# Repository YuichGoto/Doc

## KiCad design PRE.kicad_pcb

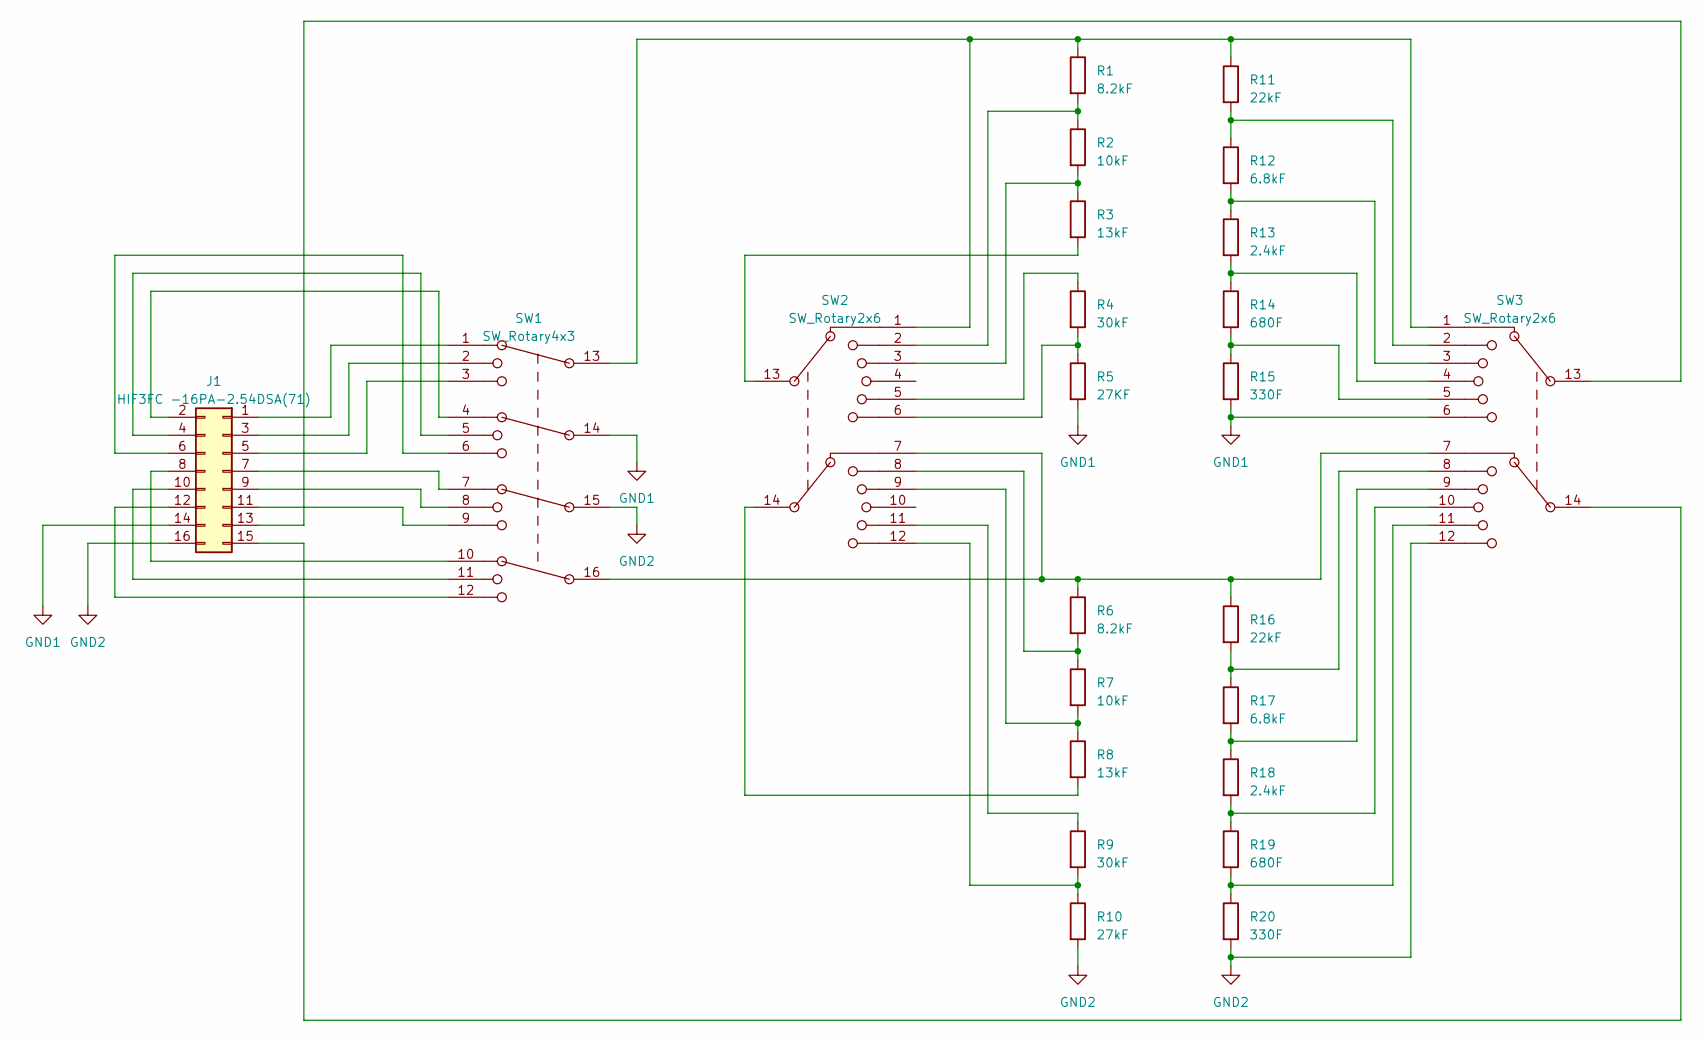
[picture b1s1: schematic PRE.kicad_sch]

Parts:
J1: HIF3FC -16PA-2.54DSA(71); PinHeader_2x08_P2.54mm_Vertical
R1, R6: 8.2kF; R_Axial_DIN0207_L6.3mm_D2.5mm_P10.16mm_Horizontal
R2, R7: 10kF; R_Axial_DIN0207_L6.3mm_D2.5mm_P10.16mm_Horizontal
R3, R8: 13kF; R_Axial_DIN0207_L6.3mm_D2.5mm_P10.16mm_Horizontal
R4, R9: 30kF; R_Axial_DIN0207_L6.3mm_D2.5mm_P10.16mm_Horizontal
R5: 27KF; R_Axial_DIN0207_L6.3mm_D2.5mm_P10.16mm_Horizontal
R10: 27kF; R_Axial_DIN0207_L6.3mm_D2.5mm_P10.16mm_Horizontal
R11, R16: 22kF; R_Axial_DIN0207_L6.3mm_D2.5mm_P10.16mm_Horizontal
R12, R17: 6.8kF; R_Axial_DIN0207_L6.3mm_D2.5mm_P10.16mm_Horizontal
R13, R18: 2.4kF; R_Axial_DIN0207_L6.3mm_D2.5mm_P10.16mm_Horizontal
R14, R19: 680F; R_Axial_DIN0207_L6.3mm_D2.5mm_P10.16mm_Horizontal
R15, R20: 330F; R_Axial_DIN0207_L6.3mm_D2.5mm_P10.16mm_Horizontal
SW1: SW_Rotary4x3
SW2, SW3: SW_Rotary2x6

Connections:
GND1: J1.14, R5.2, R15.2, SW1.14, SW3.6
GND2: J1.16, R10.2, R20.2, SW1.15, SW3.12
unnamed: J1.1, SW1.1
unnamed: J1.2, SW1.4
unnamed: J1.3, SW1.2
unnamed: J1.4, SW1.5
unnamed: J1.5, SW1.3
unnamed: J1.6, SW1.6
unnamed: J1.7, SW1.7
unnamed: J1.8, SW1.10
unnamed: J1.9, SW1.8
unnamed: J1.10, SW1.11
unnamed: J1.11, SW1.9
unnamed: J1.12, SW1.12
unnamed: J1.13, SW3.13
unnamed: J1.15, SW3.14
unnamed: R1.1, R11.1, SW1.13, SW2.1, SW3.1
unnamed: R1.2, R2.1, SW2.2
unnamed: R2.2, R3.1, SW2.3
unnamed: R3.2, SW2.13
unnamed: R4.1, SW2.5
unnamed: R4.2, R5.1, SW2.6
unnamed: R6.2, R7.1, SW2.8
unnamed: R7.2, R8.1, SW2.9
unnamed: R8.2, SW2.14
unnamed: R9.1, SW2.11
unnamed: R9.2, R10.1, SW2.12
unnamed: R11.2, R12.1, SW3.2
unnamed: R12.2, R13.1, SW3.3
unnamed: R13.2, R14.1, SW3.4
unnamed: R14.2, R15.1, SW3.5
unnamed: R6.1, R16.1, SW1.16, SW2.7, SW3.7
unnamed: R16.2, R17.1, SW3.8
unnamed: R17.2, R18.1, SW3.9
unnamed: R18.2, R19.1, SW3.10
unnamed: R19.2, R20.1, SW3.11

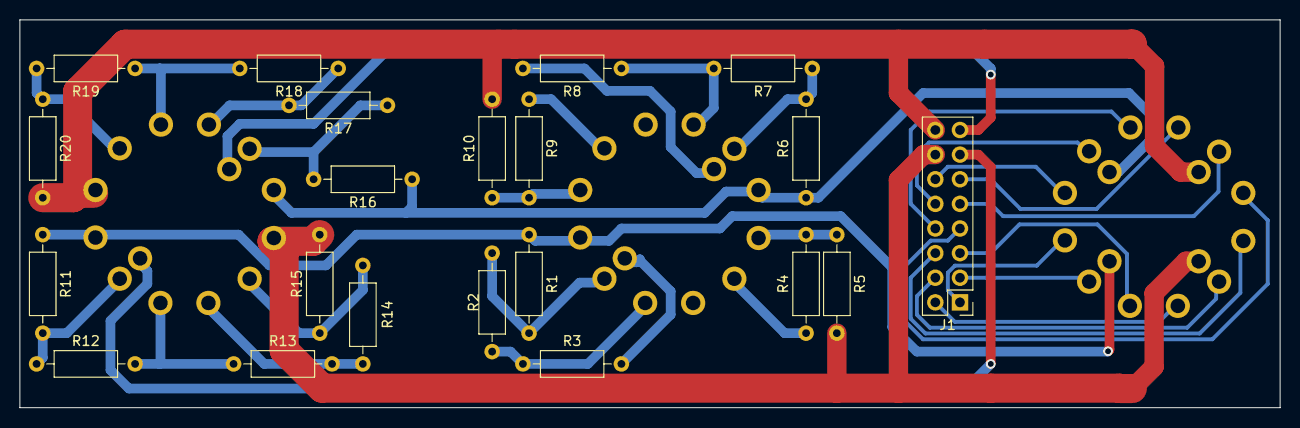
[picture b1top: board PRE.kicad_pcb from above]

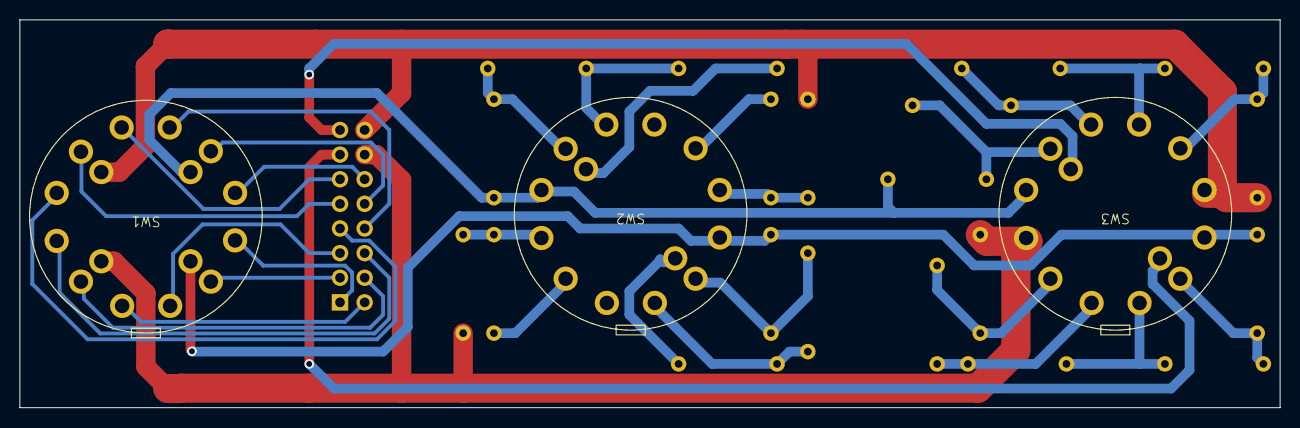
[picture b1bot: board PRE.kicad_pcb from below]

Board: 2 copper layers, 130.0 x 40.0 mm, 24 parts (3 on the bottom side), 36 nets.

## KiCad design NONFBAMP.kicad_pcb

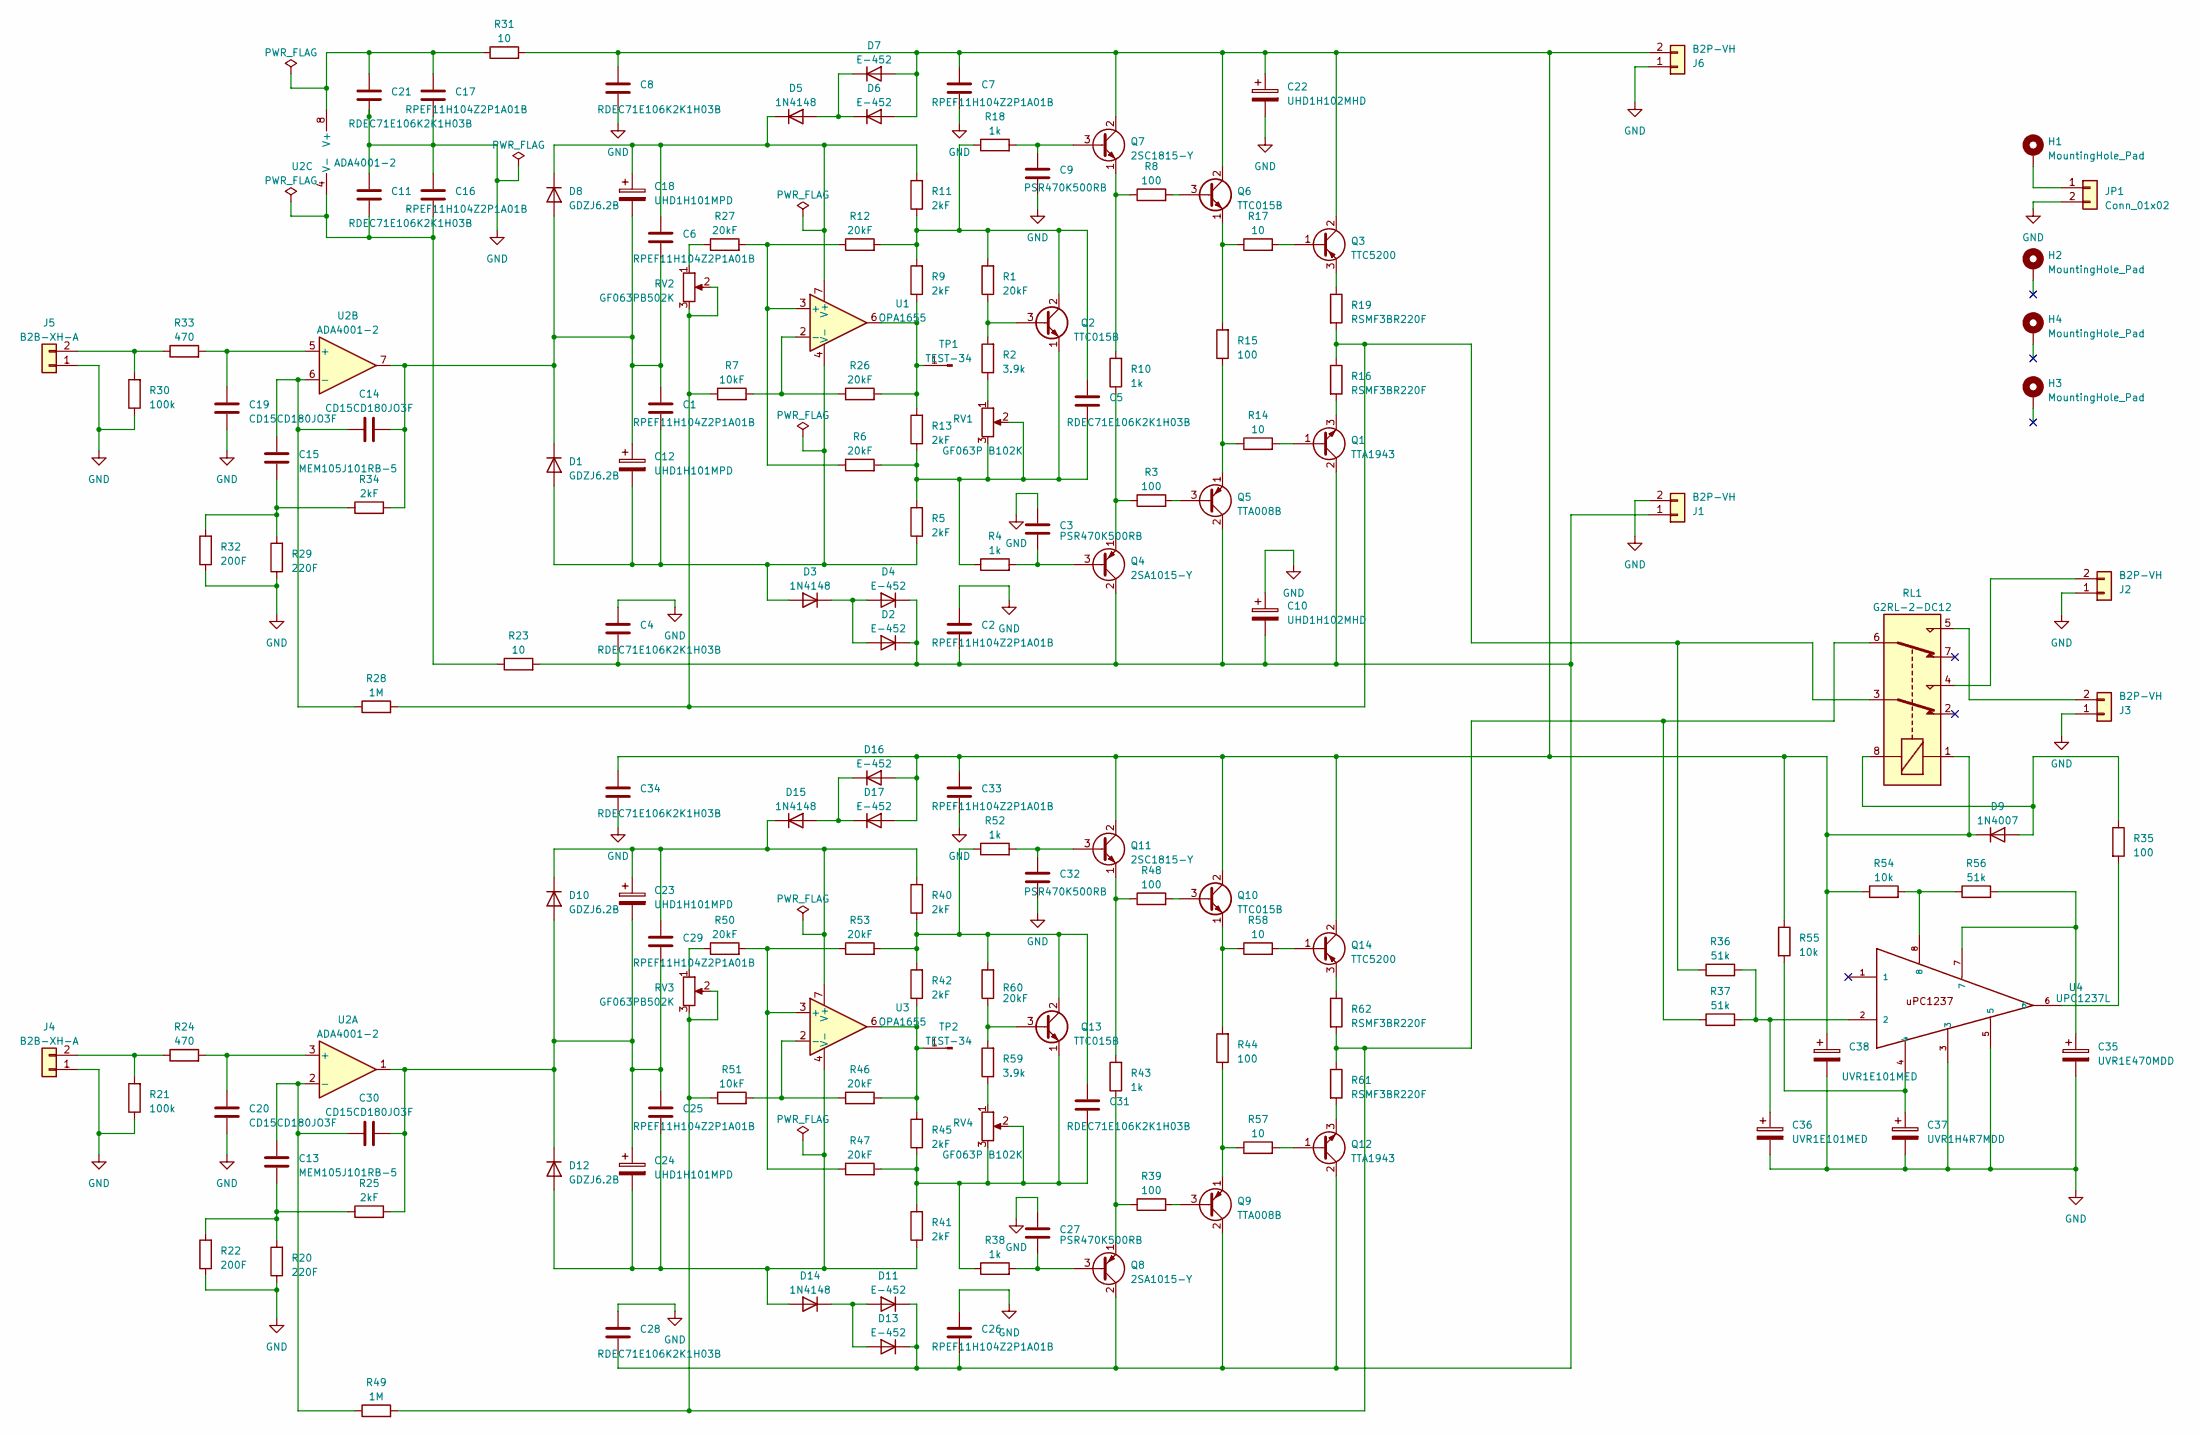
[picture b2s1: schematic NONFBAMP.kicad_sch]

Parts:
C1, C2, C6, C7, C16, C17, C25, C26, C29, C33: RPEF11H104Z2P1A01B; C_Disc_D5.0mm_W2.5mm_P2.50mm
C3, C9, C27, C32: PSR470K500RB; C_Disc_D5.0mm_W2.5mm_P5.00mm
C4, C5, C8, C11, C21, C28, C31, C34: RDEC71E106K2K1H03B; C_Disc_D5.0mm_W2.5mm_P5.00mm
C10, C22: UHD1H102MHD; CP_Radial_D16.0mm_P7.50mm
C12, C18, C23, C24: UHD1H101MPD; CP_Radial_D8.0mm_P3.50mm
C13, C15: MEM105J101RB-5; C_Rect_L7.2mm_W5.5mm_P5.00mm_FKS2_FKP2_MKS2_MKP2
C14, C19, C20, C30: CD15CD180JO3F; C_Disc_D10.5mm_W5.0mm_P5.00mm
C35: UVR1E470MDD; CP_Radial_D5.0mm_P2.50mm
C36, C38: UVR1E101MED; CP_Radial_D6.3mm_P2.50mm
C37: UVR1H4R7MDD; CP_Radial_D5.0mm_P2.50mm
D1, D8, D10, D12: GDZJ6.2B; D_DO-35_SOD27_P7.62mm_Horizontal
D2, D4, D6, D7, D11, D13, D16, D17: E-452; D_DO-35_SOD27_P7.62mm_Horizontal
D3, D5, D14, D15: 1N4148; D_DO-35_SOD27_P7.62mm_Horizontal
D9: 1N4007; D_DO-41_SOD81_P10.16mm_Horizontal
H1, H2, H3, H4: MountingHole_Pad; MountingHole_3.2mm_M3_DIN965_Pad
J1, J2, J3, J6: B2P-VH; JST_VH_B2P-VH_1x02_P3.96mm_Vertical
J4, J5: B2B-XH-A; JST_XH_B2B-XH-A_1x02_P2.50mm_Vertical
JP1: Conn_01x02; PinHeader_1x02_P2.54mm_Vertical
Q1, Q12: TTA1943; TO-3PB-3_Vertical
Q2, Q6, Q10, Q13: TTC015B; TO-126-3_Vertical
Q3, Q14: TTC5200; TO-3PB-3_Vertical
Q4, Q8: 2SA1015-Y; TO-92
Q5, Q9: TTA008B; TO-126-3_Vertical
Q7, Q11: 2SC1815-Y; TO-92
R1, R6, R12, R26, R27, R46, R47, R50, R53, R60: 20kF; R_Axial_DIN0204_L3.6mm_D1.6mm_P5.08mm_Horizontal
R2, R59: 3.9k; R_Axial_DIN0204_L3.6mm_D1.6mm_P5.08mm_Horizontal
R3, R8, R15, R35, R39, R44, R48: 100; R_Axial_DIN0204_L3.6mm_D1.6mm_P5.08mm_Horizontal
R4, R10, R18, R38, R43, R52: 1k; R_Axial_DIN0204_L3.6mm_D1.6mm_P5.08mm_Horizontal
R5, R9, R11, R13, R25, R34, R40, R41, R42, R45: 2kF; R_Axial_DIN0204_L3.6mm_D1.6mm_P5.08mm_Horizontal
R7, R51: 10kF; R_Axial_DIN0204_L3.6mm_D1.6mm_P5.08mm_Horizontal
R14, R17, R23, R31, R57, R58: 10; R_Axial_DIN0204_L3.6mm_D1.6mm_P5.08mm_Horizontal
R16, R19, R61, R62: RSMF3BR220F; R_Axial_DIN0516_L15.5mm_D5.0mm_P20.32mm_Horizontal
R20, R29: 220F; R_Axial_DIN0204_L3.6mm_D1.6mm_P5.08mm_Horizontal
R21, R30: 100k; R_Axial_DIN0204_L3.6mm_D1.6mm_P5.08mm_Horizontal
R22, R32: 200F; R_Axial_DIN0204_L3.6mm_D1.6mm_P5.08mm_Horizontal
R24, R33: 470; R_Axial_DIN0204_L3.6mm_D1.6mm_P5.08mm_Horizontal
R28, R49: 1M; R_Axial_DIN0204_L3.6mm_D1.6mm_P5.08mm_Horizontal
R36, R37, R56: 51k; R_Axial_DIN0204_L3.6mm_D1.6mm_P5.08mm_Horizontal
R54, R55: 10k; R_Axial_DIN0204_L3.6mm_D1.6mm_P5.08mm_Horizontal
RL1: G2RL-2-DC12; Relay_DPDT_Omron_G2RL
RV1, RV4: GF063P B102K; Potentiometer_Vishay_T73YP_Vertical
RV2, RV3: GF063PB502K; Potentiometer_Vishay_T73YP_Vertical
TP1, TP2: TEST-34; PinHeader_1x01_P2.00mm_Vertical
U1, U3: OPA1655; SOIC-8_3.9x4.9mm_P1.27mm
U2: ADA4001-2; SOIC-8_3.9x4.9mm_P1.27mm
U4: UPC1237L; SIP-8_19x3mm_P2.54mm

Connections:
GND: C2.1, C3.1, C4.1, C7.2, C8.2, C9.2, C10.1, C11.1, C16.1, C17.2, C19.2, C20.2, C21.2, C22.2, C26.1, C27.1, C28.1, C32.2, C33.2, C34.2, C35.2, C36.2, C37.2, C38.2, J1.2, J2.1, J3.1, J4.1, J5.1, J6.1, JP1.2, R20.1, R21.1, R22.1, R29.1, R30.1, R32.1, U4.3, U4.5
unnamed: C17.1, C21.1, R31.1, U2.8 (V+)
unnamed: C11.2, C16.2, R23.1, U2.4 (V-)
unnamed: C6.1, C18.1, D5.1 (K), D8.1 (K), R11.2, U1.7 (V+)
unnamed: C1.2, C12.2, D1.2 (A), D3.2 (A), R5.1, U1.4 (V-)
unnamed: C23.1, C29.1, D10.1 (K), D15.1 (K), R40.2, U3.7 (V+)
unnamed: C24.2, C25.2, D12.2 (A), D14.2 (A), R41.1, U3.4 (V-)
unnamed: C13.2, R20.2, R22.2, R25.1
unnamed: C15.2, R29.2, R32.2, R34.1
unnamed: C35.1, R56.2, U4.7
unnamed: C36.1, R36.2, R37.2, U4.2
unnamed: C37.1, R55.2, U4.4
unnamed: C1.1, C6.2, C12.1, C14.2, C18.2, D1.1 (K), D8.2 (A), R34.2, U2.7
unnamed: D2.2 (A), D3.1 (K), D4.2 (A)
unnamed: D5.2 (A), D6.1 (K), D7.1 (K)
unnamed: D9.2 (A), R35.1, RL1.8
unnamed: C23.2, C24.1, C25.1, C29.2, C30.2, D10.2 (A), D12.1 (K), R25.2, U2.1
unnamed: D11.2 (A), D13.2 (A), D14.1 (K)
unnamed: C2.2, C4.2, C10.2, C26.2, C28.2, D2.1 (K), D4.1 (K), D11.1 (K), D13.1 (K), J1.1, Q1.2 (C), Q4.2 (C), Q5.2 (C), Q8.2 (C), Q9.2 (C), Q12.2 (C), R23.2
unnamed: D15.2 (A), D16.1 (K), D17.1 (K)
unnamed: C7.1, C8.1, C22.1, C33.1, C34.1, C38.1, D6.2 (A), D7.2 (A), D9.1 (K), D16.2 (A), D17.2 (A), J6.2, Q3.2 (C), Q6.2 (C), Q7.2 (C), Q10.2 (C), Q11.2 (C), Q14.2 (C), R31.2, R54.1, R55.1, RL1.1
unnamed: J2.2, RL1.4
unnamed: J3.2, RL1.5
unnamed: J4.2, R21.2, R24.1
unnamed: J5.2, R30.2, R33.1
unnamed: H1.1, JP1.1
unnamed: Q1.1 (B), R14.2
unnamed: Q1.3 (E), R16.2
unnamed: Q2.3 (B), R1.1, R2.2
unnamed: C5.1, Q2.2 (C), R1.2, R9.2, R11.1, R12.2, R18.1
unnamed: C5.2, Q2.1 (E), R4.1, R5.2, R6.2, R13.1, RV1.2, RV1.3
unnamed: Q3.1 (B), R17.2
unnamed: Q3.3 (E), R19.1
unnamed: C3.2, Q4.3 (B), R4.2
unnamed: Q4.1 (E), R3.1, R10.1
unnamed: Q5.3 (B), R3.2
unnamed: Q5.1 (E), R14.1, R15.1
unnamed: Q6.3 (B), R8.2
unnamed: Q6.1 (E), R15.2, R17.1
unnamed: C9.1, Q7.3 (B), R18.2
unnamed: Q7.1 (E), R8.1, R10.2
unnamed: C27.2, Q8.3 (B), R38.2
unnamed: Q8.1 (E), R39.1, R43.1
unnamed: Q9.3 (B), R39.2
unnamed: Q9.1 (E), R44.1, R57.1
unnamed: Q10.3 (B), R48.2
unnamed: Q10.1 (E), R44.2, R58.1
unnamed: C32.1, Q11.3 (B), R52.2
unnamed: Q11.1 (E), R43.2, R48.1
unnamed: Q12.1 (B), R57.2
unnamed: Q12.3 (E), R61.2
unnamed: Q13.3 (B), R59.2, R60.1
unnamed: C31.1, Q13.2 (C), R40.1, R42.2, R52.1, R53.2, R60.2
unnamed: C31.2, Q13.1 (E), R38.1, R41.2, R45.1, R47.2, RV4.2, RV4.3
unnamed: Q14.1 (B), R58.2
unnamed: Q14.3 (E), R62.1
unnamed: R2.1, RV1.1
unnamed: R7.1, R16.1, R19.2, R28.2, R36.1, RL1.3, RV2.2, RV2.3
unnamed: R27.1, RV2.1
unnamed: R35.2, U4.6
unnamed: R37.1, R49.2, R51.1, R61.1, R62.2, RL1.6, RV3.2, RV3.3
unnamed: R50.1, RV3.1
unnamed: R54.2, R56.1, U4.8
unnamed: R59.1, RV4.1
unnamed: R9.1, R13.2, R26.2, TP1.1, U1.6
unnamed: R42.1, R45.2, R46.2, TP2.1, U3.6
unnamed: R6.1, R12.1, R27.2, U1.3 (+)
unnamed: R7.2, R26.1, U1.2 (-)
unnamed: C20.1, R24.2, U2.3 (+)
unnamed: C13.1, C30.1, R49.1, U2.2 (-)
unnamed: C19.1, R33.2, U2.5 (+)
unnamed: C14.1, C15.1, R28.1, U2.6 (-)
unnamed: R47.1, R50.2, R53.1, U3.3 (+)
unnamed: R46.1, R51.2, U3.2 (-)

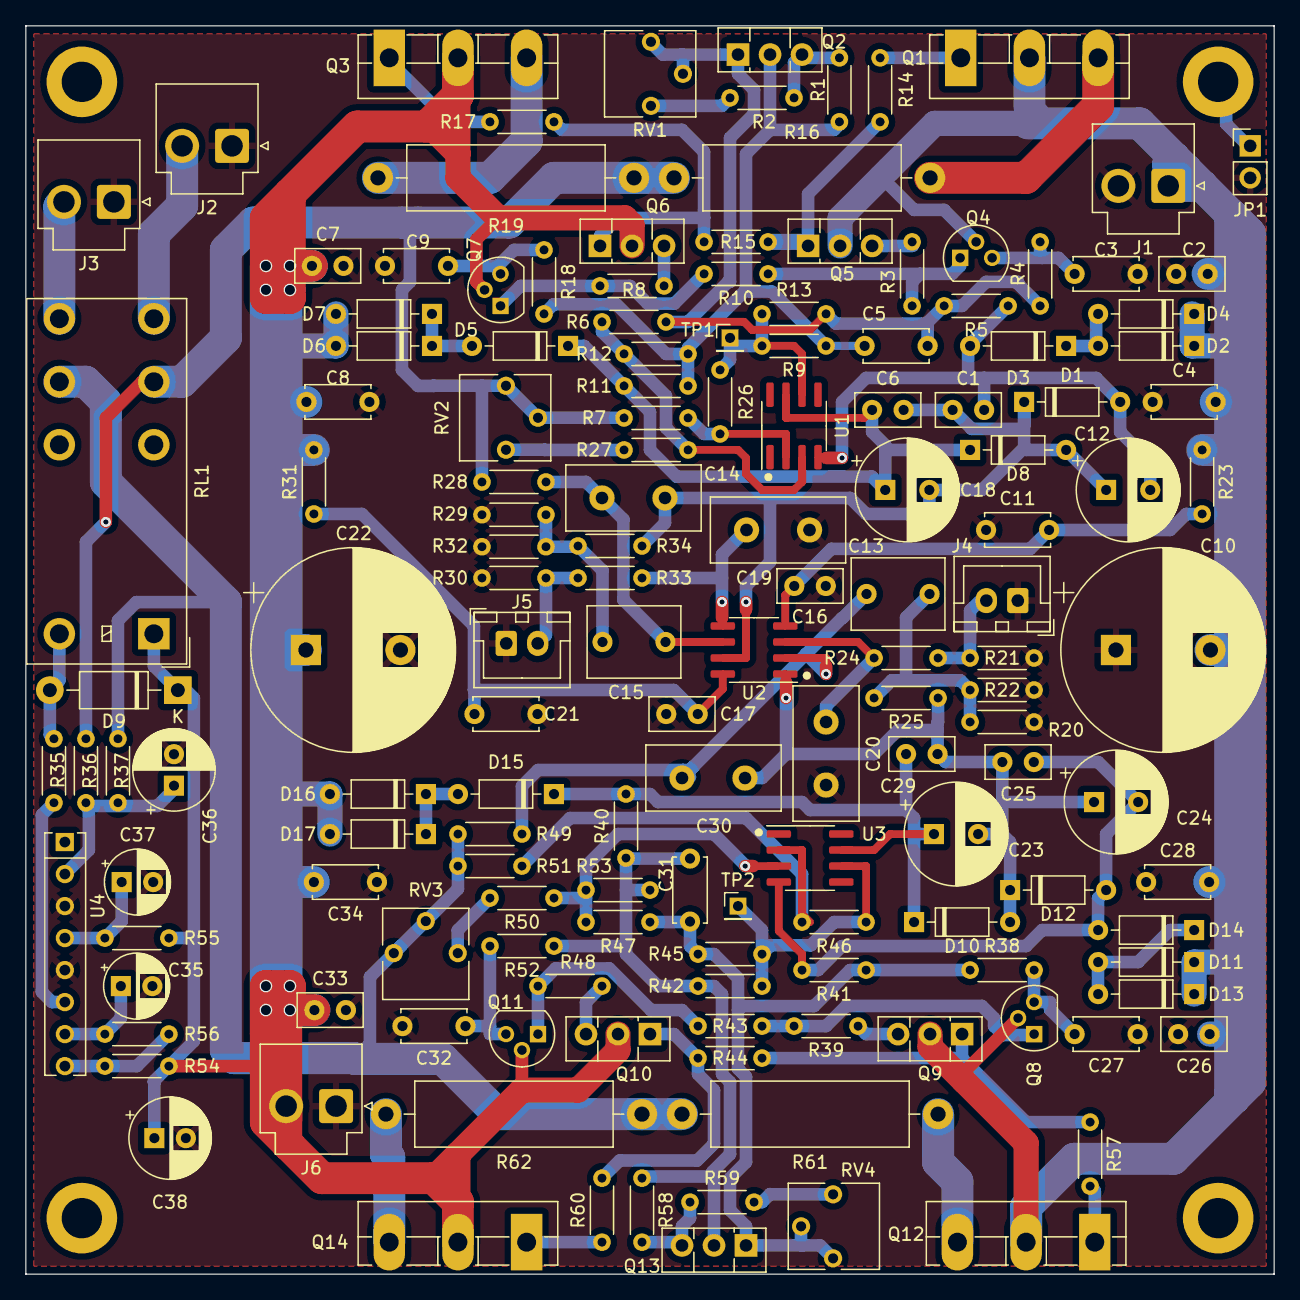
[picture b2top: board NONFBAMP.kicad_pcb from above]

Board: 2 copper layers, 99.1 x 99.1 mm, 153 parts (0 on the bottom side), 74 nets.
